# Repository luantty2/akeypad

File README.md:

# akeypad

8khz polling rate keypad, uses STM32F405 and USB3300, powered by QMK.

This project is just a prototype, cases, plates and other keyboard components are not included.

## PCB

## Firmware

The code can be found on my [Fork](https://github.com/luantty2/qmk_firmware/tree/qmk_master_build_2022q4/keyboards/akeypad).

## Bootloader

STM32f405/7xx should comes with a built-in bootloader, but sadly it doesn't seem to work on USB HS interface, if someone uses the default bootloader, he has to manually switch to FS port to upload firmware, then switch back to HS port to use his keyboard.

To address the issue, we can use a mux chip with tinyuf2 bootloader to automatically do that trick, then you don't bother switching port.

The mux chip we used here is TS3USB221, connect its 'S' pin to B14 of STM32. In normal operation, pull the pin to low to select HS interface, in bootloader mode, write this pin to high to select FS interface.

The tinyuf2 bootloader code can be found [here](https://github.com/luantty2/tinyuf2/tree/master_build/ports/stm32f4/boards/akeypad), if you wish to change B14 to other pin, you can modify it in `board.h`.

```c
//--------------------------------------------------------------------+
// Custom GPIO, used for USB mux
//--------------------------------------------------------------------+

#define CUSTOM_GPIO_PORT      GPIOB
#define CUSTOM_GPIO_PIN       GPIO_PIN_14
```

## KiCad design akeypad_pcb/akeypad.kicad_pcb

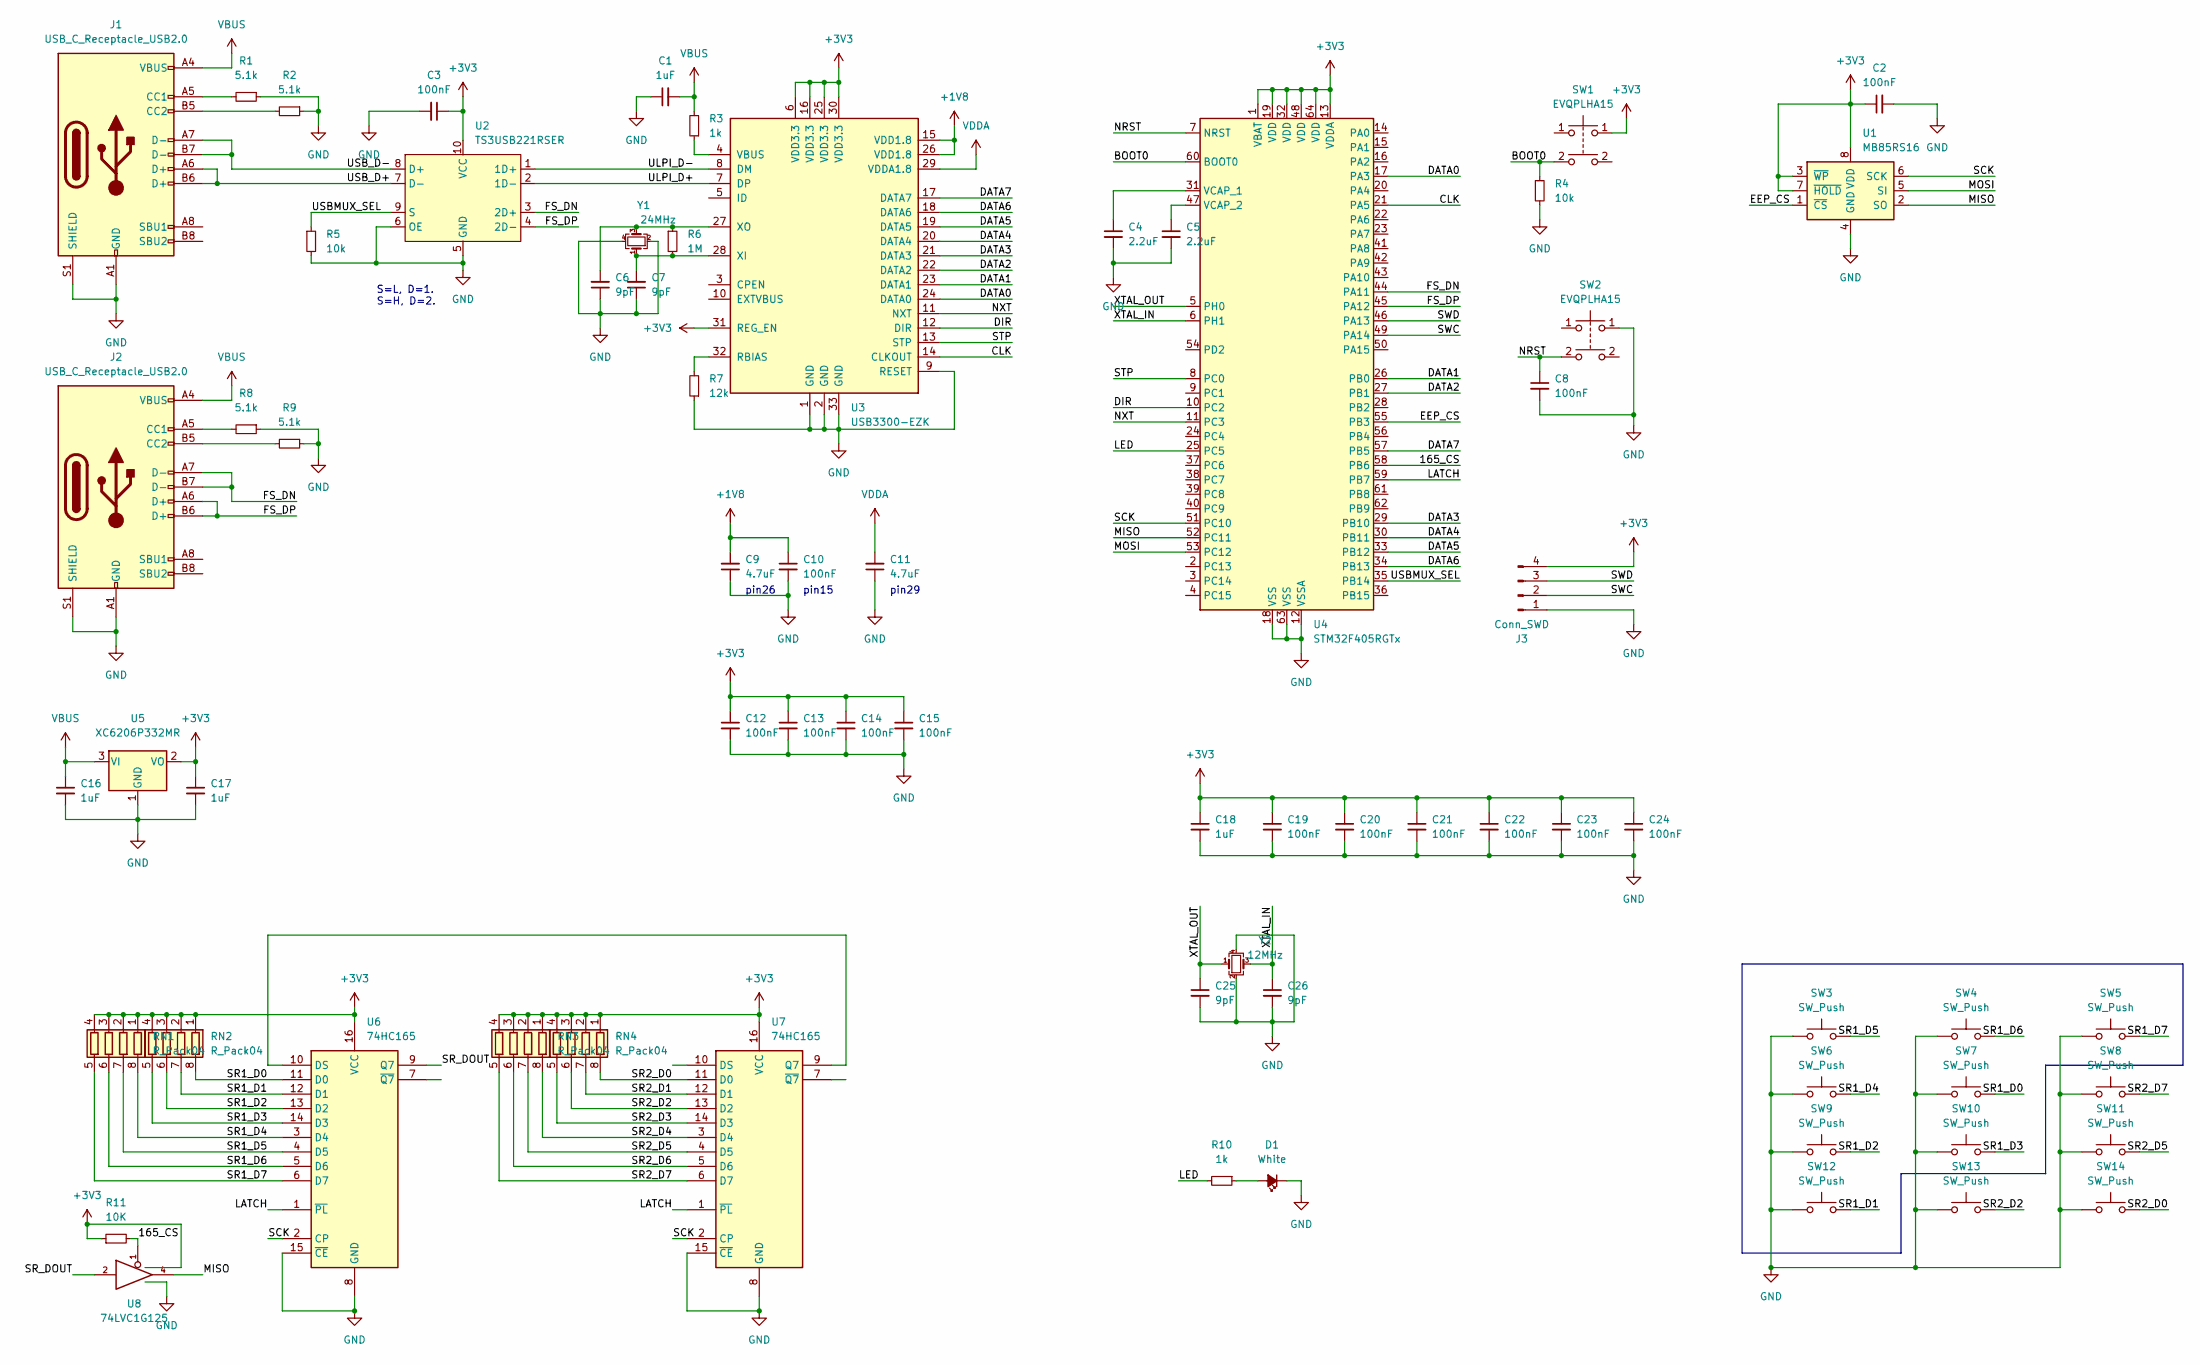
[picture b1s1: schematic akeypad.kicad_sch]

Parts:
C1, C16, C17, C18: 1uF; C_0603_1608Metric
C2, C3, C8, C10, C12, C13, C14, C15, C19, C20, C21, C22, C23, C24: 100nF; C_0402_1005Metric
C4, C5: 2.2uF; C_0603_1608Metric
C6, C7, C25, C26: 9pF; C_0402_1005Metric
C9, C11: 4.7uF; C_0603_1608Metric
D1: White; LED_0402_1005Metric
J1, J2: USB_C_Receptacle_USB2.0; USB_C_Receptacle_HRO_TYPE-C-31-M-12
J3: Conn_SWD; PinHeader_1x04_P1.27mm_Vertical
R1, R2, R8, R9: 5.1k; R_0402_1005Metric
R3, R10: 1k; R_0402_1005Metric
R4, R5: 10k; R_0402_1005Metric
R6: 1M; R_0402_1005Metric
R7: 12k; R_0402_1005Metric
R11: 10K; R_0402_1005Metric
RN1, RN2, RN3, RN4: R_Pack04; R_Array_Convex_4x0603
SW1, SW2: EVQPLHA15; SW_SPST_Panasonic_EVQPL_3PL_5PL_PT_A15
SW3, SW4, SW5, SW6, SW7, SW8, SW9, SW10, SW11, SW12, SW13, SW14: SW_Push; MXOnly-1U-NoLED
U1: MB85RS16; SOIC-8_3.9x4.9mm_P1.27mm
U2: TS3USB221RSER; UQFN-10
U3: USB3300-EZK; QFN-32-1EP_5x5mm_P0.5mm_EP3.45x3.45mm
U4: STM32F405RGTx; LQFP-64_10x10mm_P0.5mm
U5: XC6206P332MR; SOT-23
U6, U7: 74HC165; SOP-16_3.9x9.9mm_P1.27mm
U8: 74LVC1G125; SOT-23-5
Y1: 24MHz; Crystal_SMD_2016-4Pin_2.0x1.6mm
Y2: 12MHz; Crystal_SMD_3225-4Pin_3.2x2.5mm

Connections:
+1V8: C9.2, C10.1, U3.15 (VDD1.8), U3.26 (VDD1.8)
+3V3: C2.1, C3.1, C12.1, C13.1, C14.1, C15.1, C17.1, C18.1, C19.1, C20.1, C21.1, C22.1, C23.1, C24.1, J3.4, R11.1, RN1.1 (R1.1), RN1.2 (R2.1), RN1.3 (R3.1), RN1.4 (R4.1), RN2.1 (R1.1), RN2.2 (R2.1), RN2.3 (R3.1), RN2.4 (R4.1), RN3.1 (R1.1), RN3.2 (R2.1), RN3.3 (R3.1), RN3.4 (R4.1), RN4.1 (R1.1), RN4.2 (R2.1), RN4.3 (R3.1), RN4.4 (R4.1), SW1.1, U1.3 (~WP), U1.7 (~HOLD), U1.8 (VDD), U2.10 (VCC), U3.6 (VDD3.3), U3.16 (VDD3.3), U3.25 (VDD3.3), U3.30 (VDD3.3), U3.31 (REG_EN), U4.1 (VBAT), U4.13 (VDDA), U4.19 (VDD), U4.32 (VDD), U4.48 (VDD), U4.64 (VDD), U5.2 (VO), U6.16 (VCC), U7.16 (VCC), U8.5 (VCC)
/165_CS: R11.2, U4.58 (PB6), U8.1
/BOOT0: R4.1, SW1.2, U4.60 (BOOT0)
/CLK: U3.14 (CLKOUT), U4.21 (PA5)
/DATA0: U3.24 (DATA0), U4.17 (PA3)
/DATA1: U3.23 (DATA1), U4.26 (PB0)
/DATA2: U3.22 (DATA2), U4.27 (PB1)
/DATA3: U3.21 (DATA3), U4.29 (PB10)
/DATA4: U3.20 (DATA4), U4.30 (PB11)
/DATA5: U3.19 (DATA5), U4.33 (PB12)
/DATA6: U3.18 (DATA6), U4.34 (PB13)
/DATA7: U3.17 (DATA7), U4.57 (PB5)
/DIR: U3.12 (DIR), U4.10 (PC2)
/EEP_CS: U1.1 (~CS), U4.55 (PB3)
/FS_DN: J2.A7 (D-), J2.B7 (D-), U2.3 (2D+), U4.44 (PA11)
/FS_DP: J2.A6 (D+), J2.B6 (D+), U2.4 (2D-), U4.45 (PA12)
/LATCH: U4.59 (PB7), U6.1 (~PL), U7.1 (~PL)
/LED: R10.2, U4.25 (PC5)
/MISO: U1.2 (SO), U4.52 (PC11), U8.4
/MOSI: U1.5 (SI), U4.53 (PC12)
/NRST: C8.1, SW2.2, U4.7 (NRST)
/NXT: U3.11 (NXT), U4.11 (PC3)
/SCK: U1.6 (SCK), U4.51 (PC10), U6.2 (CP), U7.2 (CP)
/SR1_D0: RN2.8 (R1.2), SW7.2, U6.11 (D0)
/SR1_D1: RN2.7 (R2.2), SW12.2, U6.12 (D1)
/SR1_D2: RN2.6 (R3.2), SW9.2, U6.13 (D2)
/SR1_D3: RN2.5 (R4.2), SW10.2, U6.14 (D3)
/SR1_D4: RN1.8 (R1.2), SW6.2, U6.3 (D4)
/SR1_D5: RN1.7 (R2.2), SW3.2, U6.4 (D5)
/SR1_D6: RN1.6 (R3.2), SW4.2, U6.5 (D6)
/SR1_D7: RN1.5 (R4.2), SW5.2, U6.6 (D7)
/SR2_D0: RN4.8 (R1.2), SW14.2, U7.11 (D0)
/SR2_D1: RN4.7 (R2.2), U7.12 (D1)
/SR2_D2: RN4.6 (R3.2), SW13.2, U7.13 (D2)
/SR2_D3: RN4.5 (R4.2), U7.14 (D3)
/SR2_D4: RN3.8 (R1.2), U7.3 (D4)
/SR2_D5: RN3.7 (R2.2), SW11.2, U7.4 (D5)
/SR2_D6: RN3.6 (R3.2), U7.5 (D6)
/SR2_D7: RN3.5 (R4.2), SW8.2, U7.6 (D7)
/SR_DOUT: U6.9 (Q7), U8.2
/STP: U3.13 (STP), U4.8 (PC0)
/SWC: J3.2, U4.49 (PA14)
/SWD: J3.3, U4.46 (PA13)
/ULPI_D+: U2.2 (1D-), U3.7 (DP)
/ULPI_D-: U2.1 (1D+), U3.8 (DM)
/USBMUX_SEL: R5.1, U2.9 (S), U4.35 (PB14)
/USB_D+: J1.A6 (D+), J1.B6 (D+), U2.7 (D-)
/USB_D-: J1.A7 (D-), J1.B7 (D-), U2.8 (D+)
/XTAL_IN: C26.1, U4.6 (PH1), Y2.3
/XTAL_OUT: C25.1, U4.5 (PH0), Y2.1
GND: C1.1, C2.2, C3.2, C4.2, C5.2, C6.1, C7.1, C8.2, C9.1, C10.2, C11.1, C12.2, C13.2, C14.2, C15.2, C16.2, C17.2, C18.2, C19.2, C20.2, C21.2, C22.2, C23.2, C24.2, C25.2, C26.2, D1.1 (K), J1.A1 (GND), J1.A12 (GND), J1.B1 (GND), J1.B12 (GND), J1.S1 (SHIELD), J2.A1 (GND), J2.A12 (GND), J2.B1 (GND), J2.B12 (GND), J2.S1 (SHIELD), J3.1, R1.1, R2.1, R4.2, R5.2, R7.1, R8.1, R9.1, SW2.1, SW3.1, SW4.1, SW5.1, SW6.1, SW7.1, SW8.1, SW9.1, SW10.1, SW11.1, SW12.1, SW13.1, SW14.1, U1.4 (GND), U2.5 (GND), U2.6 (OE), U3.1 (GND), U3.2 (GND), U3.9 (RESET), U3.33 (GND), U4.12 (VSSA), U4.18 (VSS), U4.63 (VSS), U5.1 (GND), U6.8 (GND), U6.15 (~CE), U7.8 (GND), U7.15 (~CE), U8.3 (GND), Y1.2, Y1.4, Y2.2, Y2.4
unnamed: C4.1, U4.31 (VCAP_1)
unnamed: C5.1, U4.47 (VCAP_2)
unnamed: C6.2, R6.1, U3.27 (XO), Y1.3
unnamed: C7.2, R6.2, U3.28 (XI), Y1.1
unnamed: D1.2 (A), R10.1
unnamed: J1.A5 (CC1), R1.2
unnamed: J1.B5 (CC2), R2.2
unnamed: J2.A5 (CC1), R8.2
unnamed: J2.B5 (CC2), R9.2
unnamed: R3.1, U3.4 (VBUS)
unnamed: R7.2, U3.32 (RBIAS)
unnamed: U6.10 (DS), U7.9 (Q7)
VBUS: C1.2, C16.1, J1.A4 (VBUS), J1.A9 (VBUS), J1.B4 (VBUS), J1.B9 (VBUS), J2.A4 (VBUS), J2.A9 (VBUS), J2.B4 (VBUS), J2.B9 (VBUS), R3.2, U5.3 (VI)
VDDA: C11.2, U3.29 (VDDA1.8)

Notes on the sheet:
pin15
pin26
pin29
S=L, D=1. S=H, D=2.

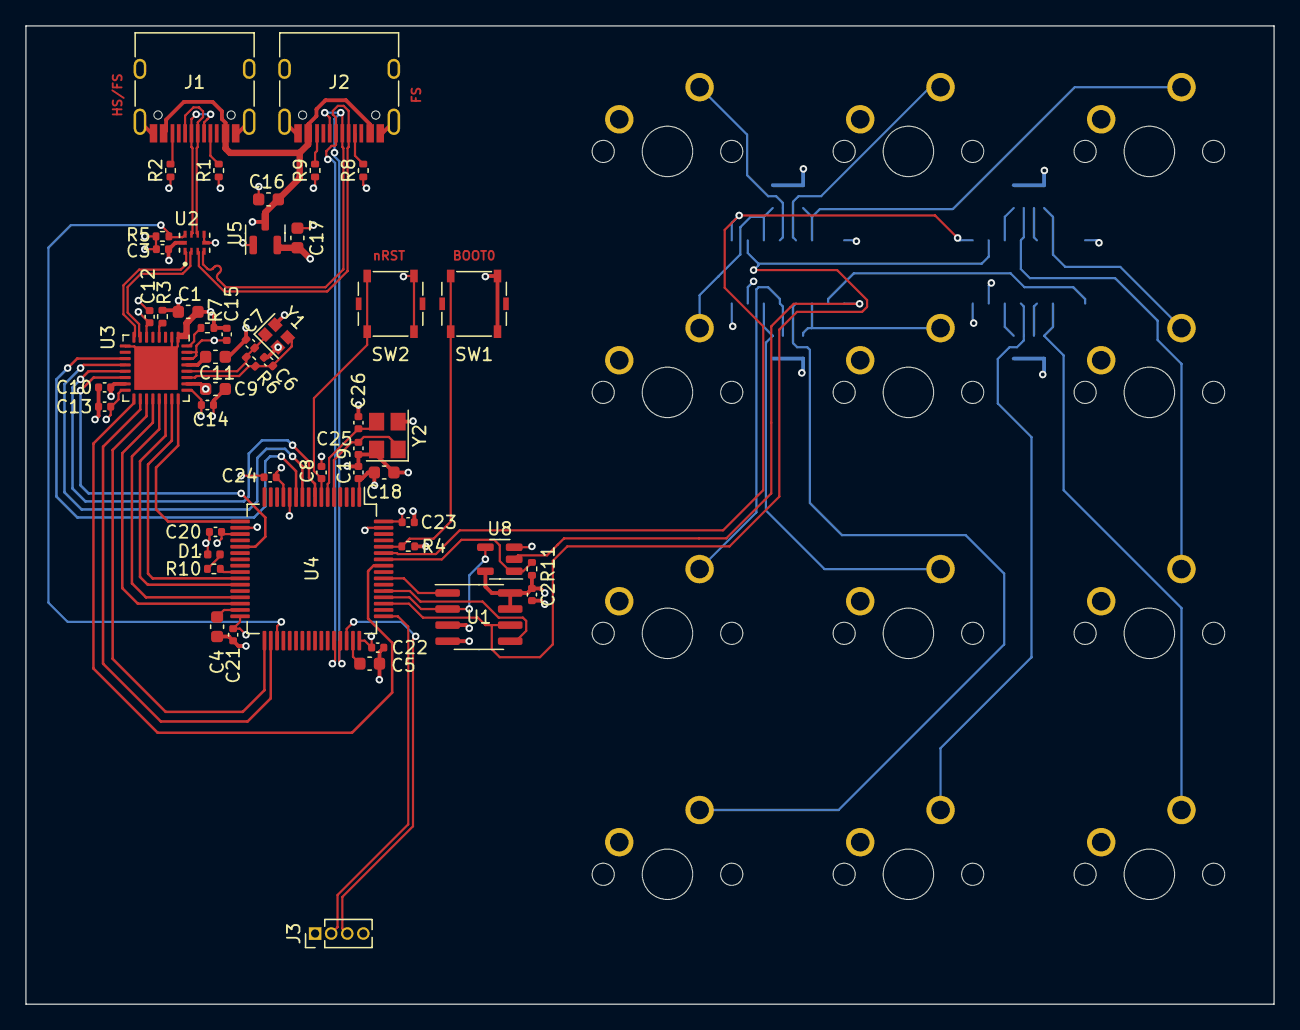
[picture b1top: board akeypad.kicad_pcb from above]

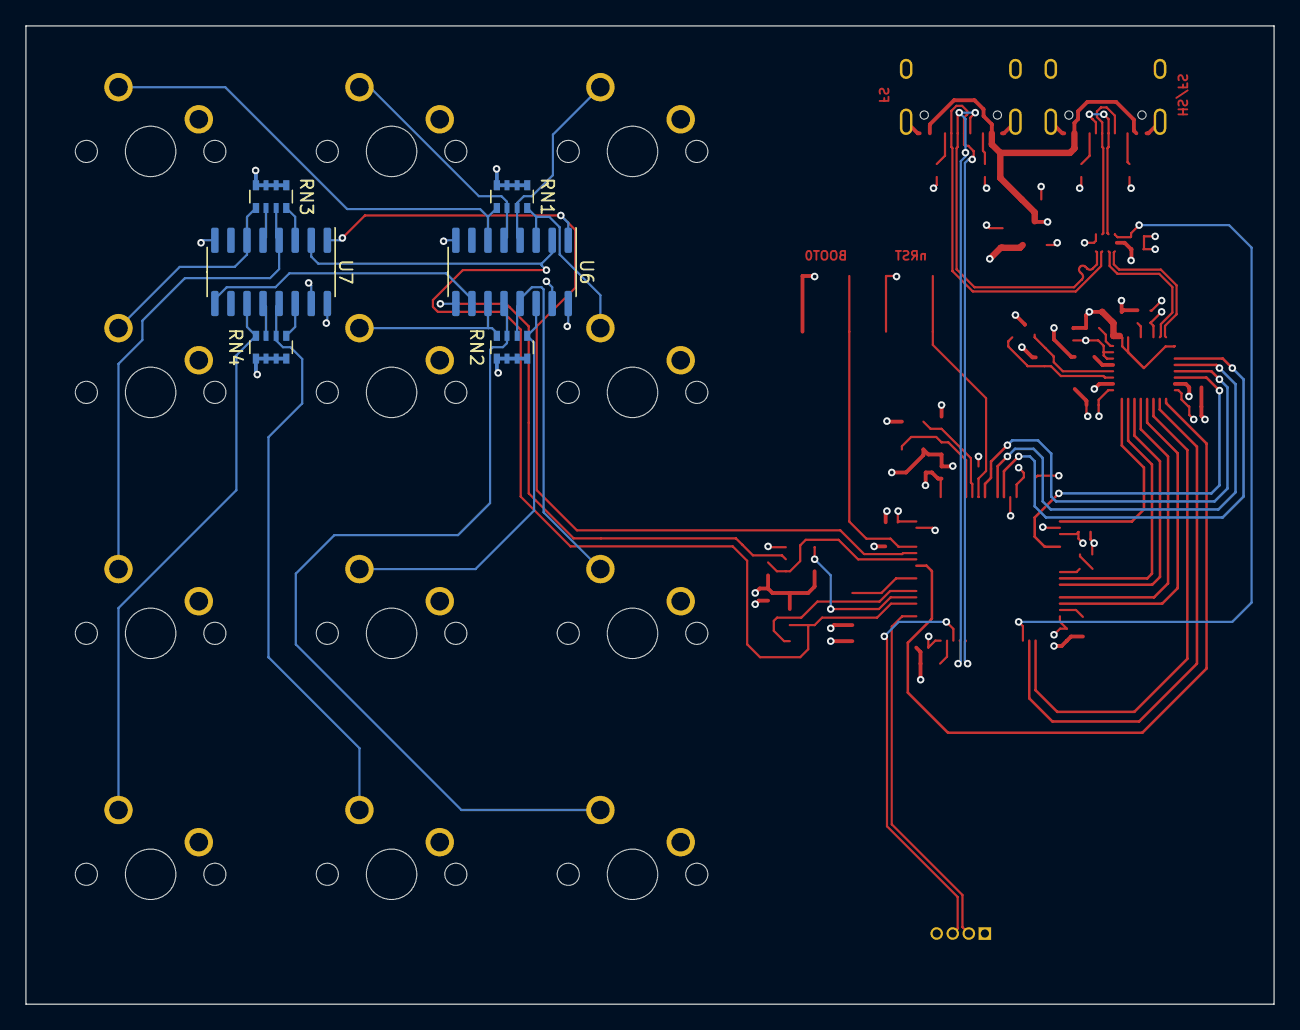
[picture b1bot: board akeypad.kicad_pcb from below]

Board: 4 copper layers, 98.7 x 77.3 mm, 69 parts (6 on the bottom side), 66 nets.

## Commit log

2023-01-15 init
2023-01-15 Create LICENSE
